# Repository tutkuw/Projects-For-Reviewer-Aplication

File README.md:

I put together this quick macropad PCB in KiCad as a hardware design sample. It pairs a bottom-mounted ESP32 with 9 Cherry MX switches, a bare EC11 rotary encoder, and a 128×32 I2C OLED on the front, using direct GPIO inputs with internal pull-ups.

Also, i auto routed it bc i dint have much time (thats why its so ugly).

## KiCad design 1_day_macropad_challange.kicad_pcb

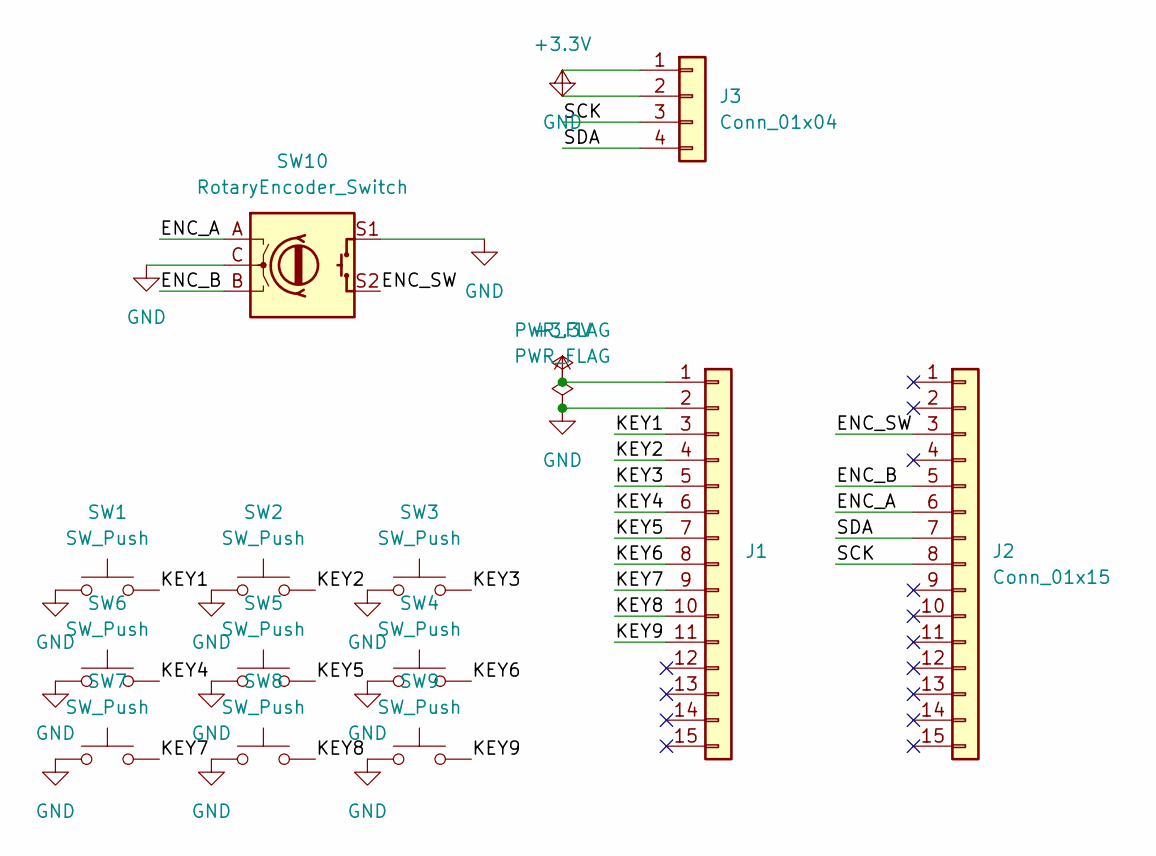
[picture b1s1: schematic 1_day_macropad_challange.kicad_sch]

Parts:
J1, J2: Conn_01x15; PinSocket_1x15_P2.54mm_Vertical
J3: Conn_01x04; PinSocket_1x04_P2.54mm_Vertical
SW1, SW2, SW3, SW4, SW5, SW6, SW7, SW8, SW9: SW_Push; SW_Cherry_MX_1.00u_PCB
SW10: RotaryEncoder_Switch; RotaryEncoder_Alps_EC11E-Switch_Vertical_H20mm

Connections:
+3.3V: J1.1, J3.2
/ENC_A: J2.6, SW10.A
/ENC_B: J2.5, SW10.B
/ENC_SW: J2.3, SW10.S2
/KEY1: J1.3, SW1.2
/KEY2: J1.4, SW2.2
/KEY3: J1.5, SW3.2
/KEY4: J1.6, SW6.2
/KEY5: J1.7, SW5.2
/KEY6: J1.8, SW4.2
/KEY7: J1.9, SW7.2
/KEY8: J1.10, SW8.2
/KEY9: J1.11, SW9.2
/SCK: J2.8, J3.3
/SDA: J2.7, J3.4
GND: J1.2, J3.1, SW1.1, SW2.1, SW3.1, SW4.1, SW5.1, SW6.1, SW7.1, SW8.1, SW9.1, SW10.C, SW10.S1

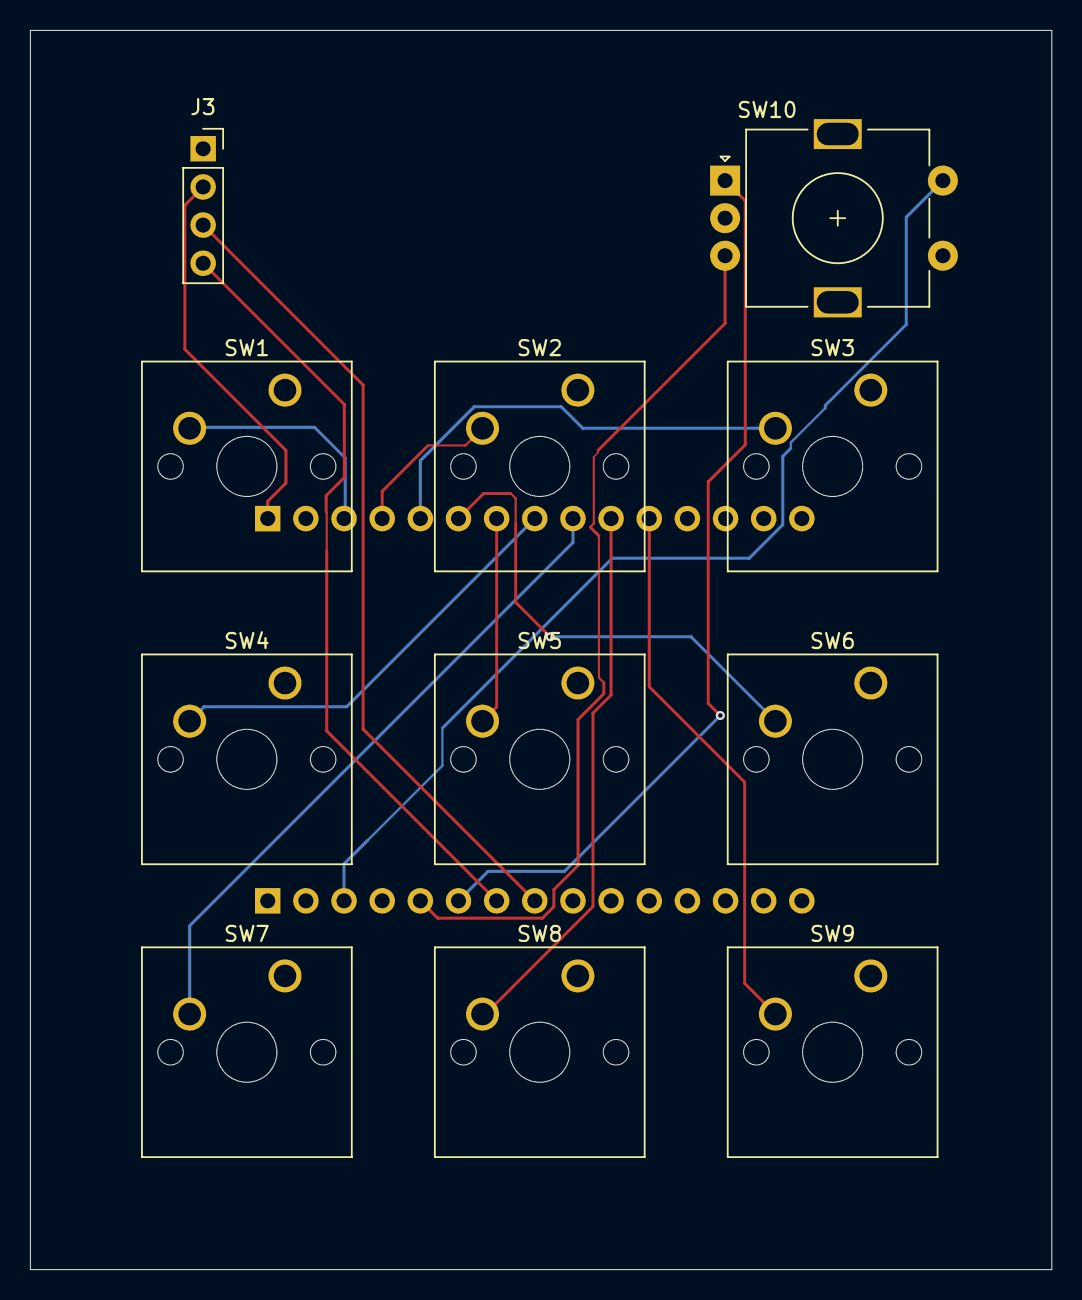
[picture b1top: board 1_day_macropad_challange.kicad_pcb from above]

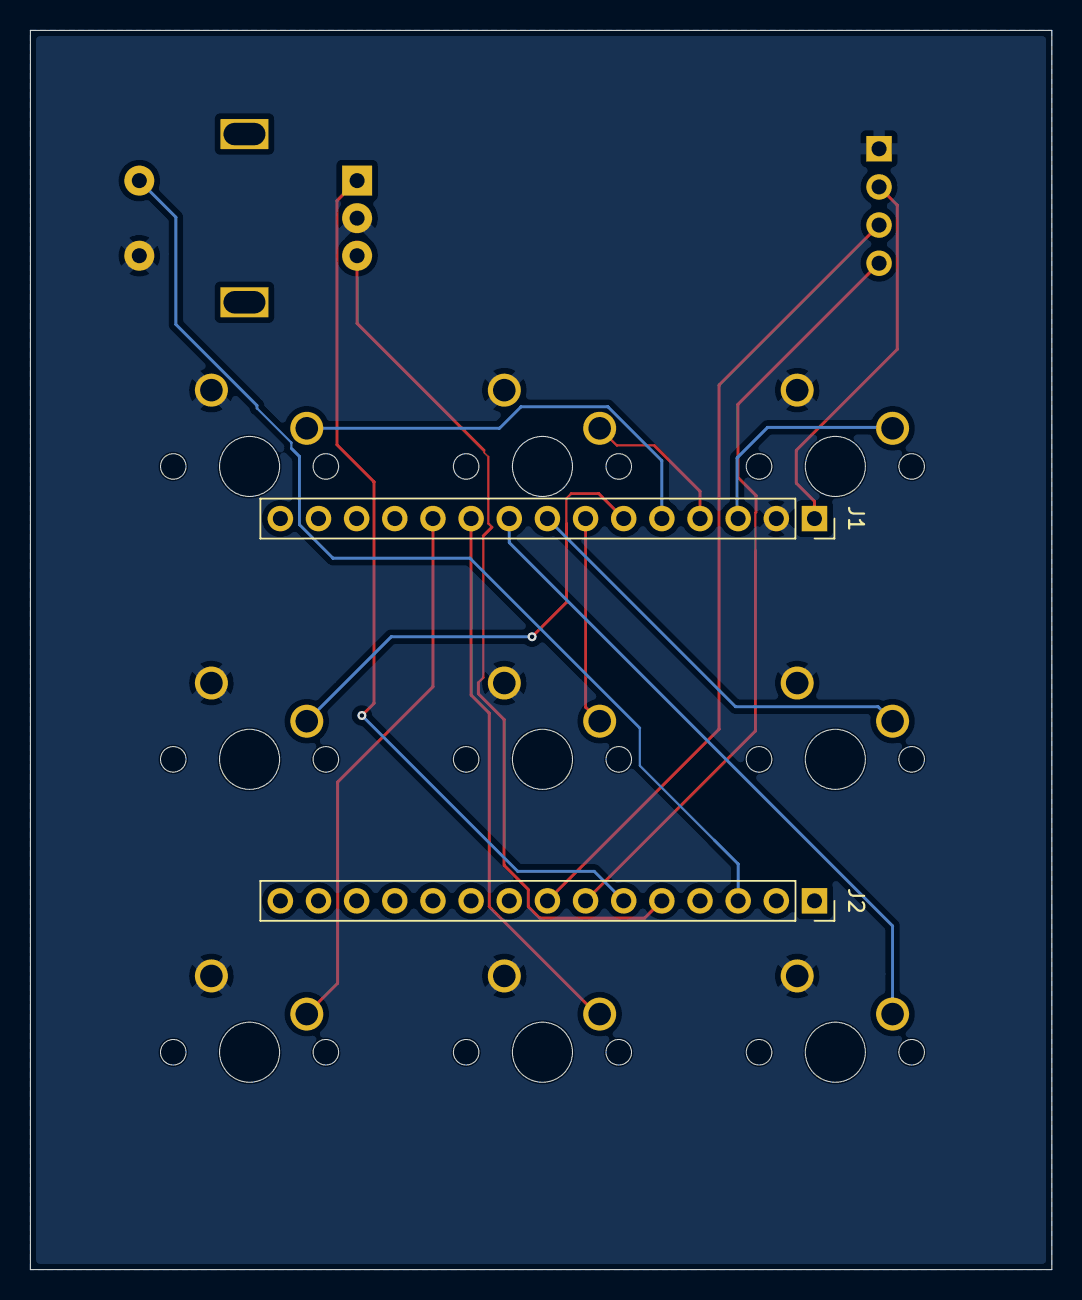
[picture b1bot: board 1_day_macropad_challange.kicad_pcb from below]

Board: 2 copper layers, 68.0 x 82.5 mm, 13 parts (2 on the bottom side), 16 nets.
